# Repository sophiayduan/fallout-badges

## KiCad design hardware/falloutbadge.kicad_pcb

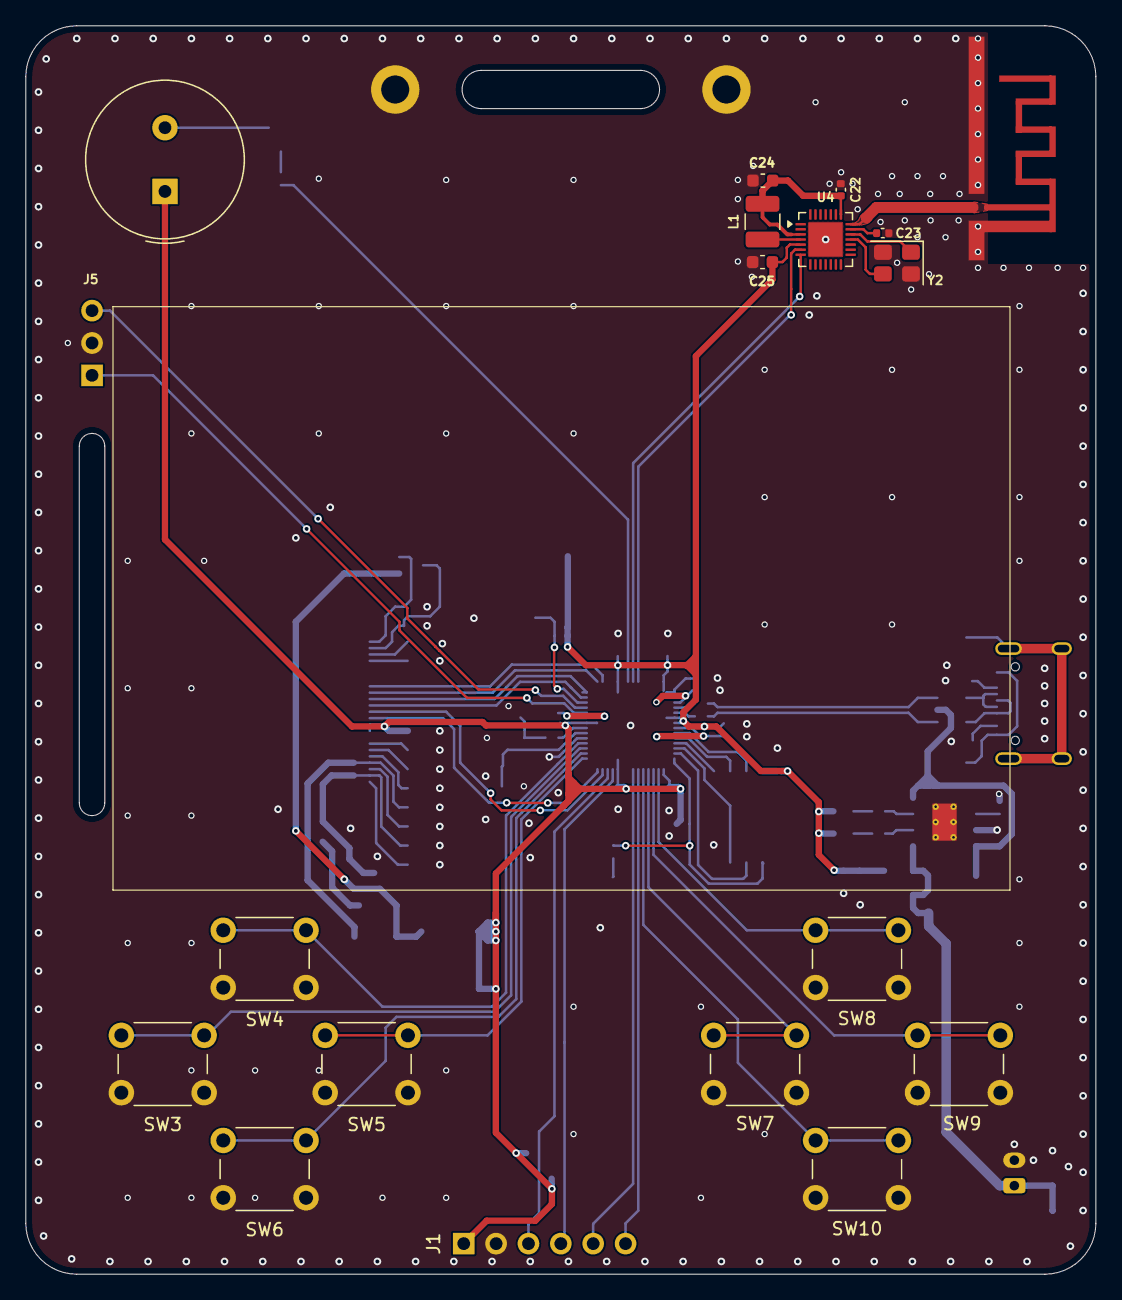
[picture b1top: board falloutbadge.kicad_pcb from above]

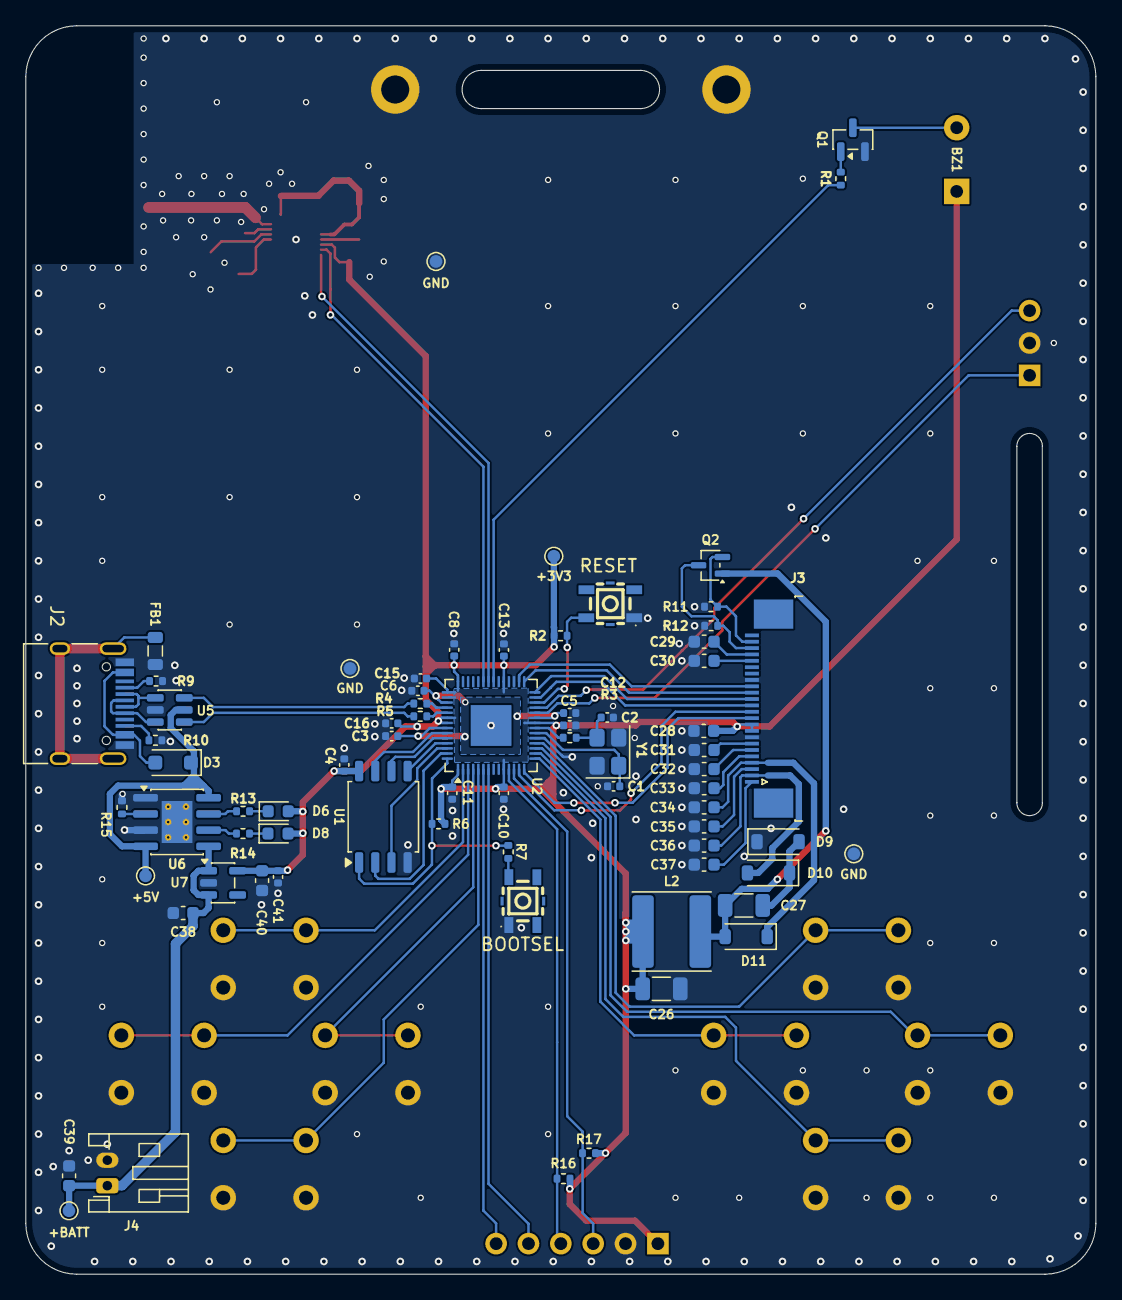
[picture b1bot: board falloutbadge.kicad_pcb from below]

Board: 2 copper layers, 84.0 x 98.0 mm, 93 parts (72 on the bottom side), 75 nets.

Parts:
+3V3: +3v3; TestPoint_Pad_D1.0mm
+5V: VBUS; TestPoint_Pad_D1.0mm
+BATT: +BATT; TestPoint_Pad_D1.0mm
AE2: Antenna_Shield; ANT-F-1-2.4G-1.6mmFR4-WCH
BOOTSEL: BOOTSEL; KEY-SMD_K2-1177SW-A4DW-06
BZ1: Buzzer; Buzzer_TDK_PS1240P02BT_D12.2mm_H6.5mm
C1, C2: 33pF; C_0402_1005Metric
C3, C4, C5, C10, C11, C12, C13, C15, C16, C22, C41: 100nF; C_0402_1005Metric
C6, C8: 1uF; C_0402_1005Metric
C23: 0.47uF; C_0402_1005Metric
C24, C38, C40: 4.7uF; C_0603_1608Metric
C25: 2.2uF; C_0603_1608Metric
C26, C27: 4.7uF; C_1206_3216Metric
C28, C29, C30, C31, C32, C33, C34, C35, C36, C37: 1uF; C_0603_1608Metric
C39: 10uF; C_0603_1608Metric
D3: D; D_SOD-123F
D6: RED; LED_0603_1608Metric
D8: NOT RED; LED_0603_1608Metric
D9, D10, D11: MBR0530; D_SOD-123
FB1: BLM18AG601SN1D; L_0805_2012Metric
GND: GND; TestPoint_Pad_D1.0mm
GND#2, GND#3: GND; TestPoint_Pad_D1.0mm
H1, H2: MountingHole; MountingHole_2.2mm_M2_DIN965_Pad
J1: Conn_02x03; PinHeader_1x06_P2.54mm_Vertical
J2: USB_C_Receptacle_USB2.0_16P; USB_C_Receptacle_HRO_TYPE-C-31-M-12
J3: E-INK; TE_2-1734839-4_1x24-1MP_P0.5mm_Horizontal
J4: LiPo; JST_PH_S2B-PH-K_1x02_P2.00mm_Horizontal
J5: Conn_01x03; PinHeader_1x03_P2.54mm_Vertical
L1: 10uH; L_1210_3225Metric
L2: 68uH; L_Changjiang_FNR6028S
Q1: AO3400A; SOT-23
Q2: Si1308EDL; SOT-323_SC-70
R1, R13, R14: 330R; R_0402_1005Metric
R2, R6, R11: 10k; R_0402_1005Metric
R3, R7: 1k; R_0402_1005Metric
R4, R5: 27.4R; R_0402_1005Metric
R9, R10: 5.1k; R_0402_1005Metric
R12: 0.47R; R_0402_1005Metric
R15: 2.2k; R_0402_1005Metric
R16, R17: 4k7; R_0402_1005Metric
RESET: RESET; KEY-SMD_K2-1177SW-A4DW-06
SW3, SW4, SW5, SW6, SW7, SW8, SW9, SW10: SW_Push; SW_PUSH_6mm
U1: W25Q32JVSS; SOIC-8_5.3x5.3mm_P1.27mm
U2: RP2040; QFN-56-1EP_7x7mm_P0.4mm_EP3.2x3.2mm
U4: CH592F; WQFN-28-1EP_4x4mm_P0.4mm_EP2.7x2.7mm
U5: USBLC6-2SC6; SOT-23-6
U6: TP4056-42-ESOP8; SOIC-8-1EP_3.9x4.9mm_P1.27mm_EP2.41x3.3mm_ThermalVias
U7: AP2112K-3.3; SOT-23-5
Y1: 12MHz; Crystal_SMD_3225-4Pin_3.2x2.5mm
Y2: 32MHz; Crystal_SMD_3225-4Pin_3.2x2.5mm

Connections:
+1V1: C3.1, C5.1, C6.1, U2.23 (DVDD), U2.45 (VREG_VOUT), U2.50 (DVDD)
+3V3: +3V3.1, BZ1.1 (+), C4.1, C8.1, C10.1, C11.1, C12.1, C13.1, C15.1, C16.1, C25.2, C26.1, C28.2, C40.2, C41.1, D6.2 (A), D8.2 (A), J1.1, J3.9, J3.10, L2.1, R2.1, R6.1, R16.1, R17.1, U1.8 (VCC), U2.1 (IOVDD), U2.10 (IOVDD), U2.22 (IOVDD), U2.33 (IOVDD), U2.42 (IOVDD), U2.43 (ADC_AVDD), U2.44 (VREG_VIN), U2.48 (USB_VDD), U2.49 (IOVDD), U4.5 (VDD33/VIO33), U7.5 (VOUT)
+BATT: +BATT.1, C38.2, C39.1, J4.1, U6.5 (BAT), U7.1 (VIN), U7.3 (EN)
/BTN1: SW3.1, U2.17 (GPIO14)
/BTN2: SW4.1, U2.18 (GPIO15)
/BTN3: SW5.1, U2.15 (GPIO12)
/BTN4: SW6.1, U2.16 (GPIO13)
/BTN5: SW7.1, U2.4 (GPIO2)
/BTN6: SW8.1, U2.2 (GPIO0)
/BTN7: SW9.1, U2.3 (GPIO1)
/BTN8: SW10.1, U2.5 (GPIO3)
/BUSY: J3.16, U2.30 (GPIO19)
/BUZ: R1.1, U2.35 (GPIO23)
/CS: J3.13, U2.27 (GPIO16)
/D+: R5.1, U5.4 (I/O2)
/D-: R4.1, U5.6 (I/O1)
/DC: J3.14, U2.28 (GPIO17)
/GDR: J3.23, Q2.2 (G), R11.1
/GPIO4: J1.6, U2.6 (GPIO4)
/GPIO5: J1.5, U2.7 (GPIO5)
/PREVGH: C34.2, D11.1 (K), J3.4
/PREVGL: C36.2, D10.2 (A), J3.2
/QSPI_SCK: U1.6 (CLK), U2.52 (QSPI_SCLK)
/QSPI_SD0: U1.5 (DI/IO_{0}), U2.53 (QSPI_SD0)
/QSPI_SD1: U1.2 (DO/IO_{1}), U2.55 (QSPI_SD1)
/QSPI_SD2: U1.3 (~WP/IO_{2}), U2.54 (QSPI_SD2)
/QSPI_SD3: U1.7 (~HOLD/~RESET/IO_{3}), U2.51 (QSPI_SD3)
/QSPI_SS: R6.2, R7.2, U1.1 (~CS), U2.56 (~QSPI_SS)
/RESE: J3.22, Q2.3 (S), R12.1
/RST: J3.15, U2.29 (GPIO18)
/SCL: J1.3, R17.2, U2.12 (GPIO9)
/SDA: J1.4, R16.2, U2.11 (GPIO8)
/SPI_MOSI: J3.11, U2.14 (GPIO11)
/SPI_SCK: J3.12, U2.13 (GPIO10)
/SWCLK: J5.1, U2.24 (SWCLK)
/SWDIO: J5.3, U2.25 (SWDIO)
/UART1_RX: U2.37 (GPIO25), U4.6 (PA8)
/UART1_TX: U2.36 (GPIO24), U4.7 (PA9)
/VDCIA: C22.2, C24.1, L1.2, U4.3 (VDCID), U4.22 (VDCIA)
/VSW: L1.1, U4.4 (VSW)
/X32MI: U4.19 (X32MI), Y2.1
/X32MO: U4.18 (~X32MO), Y2.3
GND: AE2.0 (Shield), BOOTSEL.1, C1.1, C2.1, C3.2, C4.2, C5.2, C6.2, C8.2, C10.2, C11.2, C12.2, C13.2, C15.2, C16.2, C22.1, C23.1, C24.2, C25.1, C26.2, C28.1, C29.1, C30.1, C31.1, C32.1, C33.1, C34.1, C35.1, C36.1, C37.1, C38.1, C39.2, C40.1, C41.2, D9.1 (K), FB1.2, GND.1, GND#2.1, GND#3.1, H1.1, H2.1, J1.2, J2.A1 (GND), J2.A12 (GND), J2.B1 (GND), J2.B12 (GND), J3.8, J3.17, J4.2, J5.2, Q1.2 (S), R9.2, R10.2, R11.2, R12.2, R15.2, RESET.1, SW3.2, SW4.2, SW5.2, SW6.2, SW7.2, SW8.2, SW9.2, SW10.2, U1.4 (GND), U2.19 (TESTEN), U2.31 (GPIO20), U2.57 (GND), U4.29 (GND), U5.2 (GND), U6.1 (TEMP), U6.3 (GND), U6.9 (EPAD), U7.2 (GND), Y1.2, Y1.4, Y2.2, Y2.4
unnamed: AE2.1 (A), U4.21 (ANT)
unnamed: BZ1.2 (-), Q1.3 (D)
unnamed: C2.2, R3.1, Y1.3
unnamed: D3.2 (A), J2.A4 (VBUS), J2.A9 (VBUS), J2.B4 (VBUS), J2.B9 (VBUS)
unnamed: D6.1 (K), R13.1
unnamed: D8.1 (K), R14.1
unnamed: C27.1, D9.2 (A), D10.1 (K)
unnamed: C27.2, D11.2 (A), L2.2, Q2.1 (D)
unnamed: J2.A5 (CC1), R9.1
unnamed: J2.B5 (CC2), R10.1
unnamed: J2.A6 (D+), J2.B6 (D+), U5.3 (I/O2)
unnamed: J2.A7 (D-), J2.B7 (D-), U5.1 (I/O1)
unnamed: FB1.1, J2.S1 (SHIELD)
unnamed: C37.2, J3.1
unnamed: C35.2, J3.3
unnamed: C33.2, J3.5
unnamed: C32.2, J3.6
unnamed: C31.2, J3.7
unnamed: C30.2, J3.20
unnamed: C29.2, J3.21
unnamed: Q1.1 (G), R1.2
unnamed: BOOTSEL.2, R7.1
unnamed: R2.2, RESET.2, U2.26 (RUN)
unnamed: R4.2, U2.46 (USB_DM)
unnamed: R5.2, U2.47 (USB_DP)
unnamed: C1.2, U2.20 (XIN), Y1.1
unnamed: R3.2, U2.21 (XOUT)
unnamed: C23.2, U4.20 (VINTA)
unnamed: R15.1, U6.2 (PROG)
unnamed: R13.2, U6.7 (~CHRG)
unnamed: R14.2, U6.6 (~STDBY)
VBUS: +5V.1, D3.1 (K), U5.5 (VBUS), U6.4 (V_{CC}), U6.8 (CE)

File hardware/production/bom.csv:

Designator,Footprint,Quantity,Value,LCSC Part #
AE2,ANT-F-1-2.4G-1.6mmFR4-WCH,1,Antenna_Shield,
BOOTSEL,KEY-SMD_K2-1177SW-A4DW-06,1,BOOTSEL,C92582
BZ1,Buzzer_TDK_PS1240P02BT_D12.2mm_H6.5mm,1,Buzzer,C76871 
"C1, C2",0402,2,33pF,
"C10, C11, C12, C13, C15, C16, C3, C4, C5",0402,9,100nF,
"C22, C41",0402,2,100nF,C1525
C23,0402,1,0.47uF,C92361
C24,0603,1,4.7uF,C69335
C25,0603,1,2.2uF,C23630
"C26, C27",1206,2,4.7uF,C12881
"C28, C29, C30, C31, C32, C33, C34, C35, C36, C37",0603,10,1uF,C15849
"C38, C40",0603,2,4.7uF,C19666
C39,0603,1,10uF,C19702
"C6, C8",0402,2,1uF,
"D10, D11, D9",D_SOD-123,3,MBR0530,C77336
D3,D_SOD-123F,1,D,C2892326
D6,0603,1,RED,C84269
D8,0603,1,NOT RED,C84256 
FB1,0805,1,BLM18AG601SN1D,C1017
"H1, H2",MountingHole_2.2mm_M2_DIN965_Pad,2,MountingHole,
J1,PinHeader_1x06_P2.54mm_Vertical,1,Conn_02x03,
J2,USB_C_Receptacle_HRO_TYPE-C-31-M-12,1,USB_C_Receptacle_USB2.0_16P,C165948
J3,TE_2-1734839-4_1x24-1MP_P0.5mm_Horizontal,1,E-INK,C5362165
J4,JST_PH_S2B-PH-K_1x02_P2.00mm_Horizontal,1,LiPo,C173752
J5,PinHeader_1x03_P2.54mm_Vertical,1,Conn_01x03,
L1,1210,1,10uH,C2047322
L2,L_Changjiang_FNR6028S,1,68uH,C168045
Q1,SOT-23,1,AO3400A,C20917
Q2,SOT-323_SC-70,1,Si1308EDL,C7603347
"R1, R13, R14",0402,3,330R,C208861
"R10, R9",0402,2,5.1k,C25905
R11,0402,1,10k,C25744
R12,0402,1,0.47R,C2089288
R15,0402,1,2.2k,C25879
"R16, R17",0402,2,4k7,
"R2, R6",0402,2,10k,
"R3, R7",0402,2,1k,C11702
"R4, R5",0402,2,27.4R,
RESET,KEY-SMD_K2-1177SW-A4DW-06,1,RESET,C92582
"SW10, SW3, SW4, SW5, SW6, SW7, SW8, SW9",SW_PUSH_6mm,8,SW_Push,C87494
U1,SOIC-8_5.3x5.3mm_P1.27mm,1,W25Q32JVSS,
U2,QFN-56-1EP_7x7mm_P0.4mm_EP3.2x3.2mm,1,RP2040,
U4,WQFN-28-1EP_4x4mm_P0.4mm_EP2.7x2.7mm,1,CH592F,C39831287
U5,SOT-23-6,1,USBLC6-2SC6,C2687116
U6,SOIC-8-1EP_3.9x4.9mm_P1.27mm_EP2.41x3.3mm_ThermalVias,1,TP4056-42-ESOP8,C16581
U7,SOT-23-5,1,AP2112K-3.3,C23380830
Y1,Crystal_SMD_3225-4Pin_3.2x2.5mm,1,12MHz,C9002
Y2,Crystal_SMD_3225-4Pin_3.2x2.5mm,1,32MHz,C9009

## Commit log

2026-05-01 add kicad files
2026-05-21 Add .gitignore for KiCad project files
2026-05-21 fix .gitignore auto saved files
2026-05-31 schematic with stm32
2026-06-06 vddrf1v5 and smps, + uart fix
2026-06-06 update pcb and improve power path
2026-06-06 stitching vias + drc
2026-06-07 final fixes
2026-06-08 assign lcsc parts and flip eink
2026-06-12 add v2 w/o lora
2026-06-16 final board for prod
2026-06-21 update gitignore
2026-06-21 add max's code + new 2.7" epd driver
2026-06-24 add eink test display
2026-06-24 change eink pinout to fallout
2026-06-24 add backups folder with v1
2026-06-25 new firmware?
2026-06-25 add print statement
